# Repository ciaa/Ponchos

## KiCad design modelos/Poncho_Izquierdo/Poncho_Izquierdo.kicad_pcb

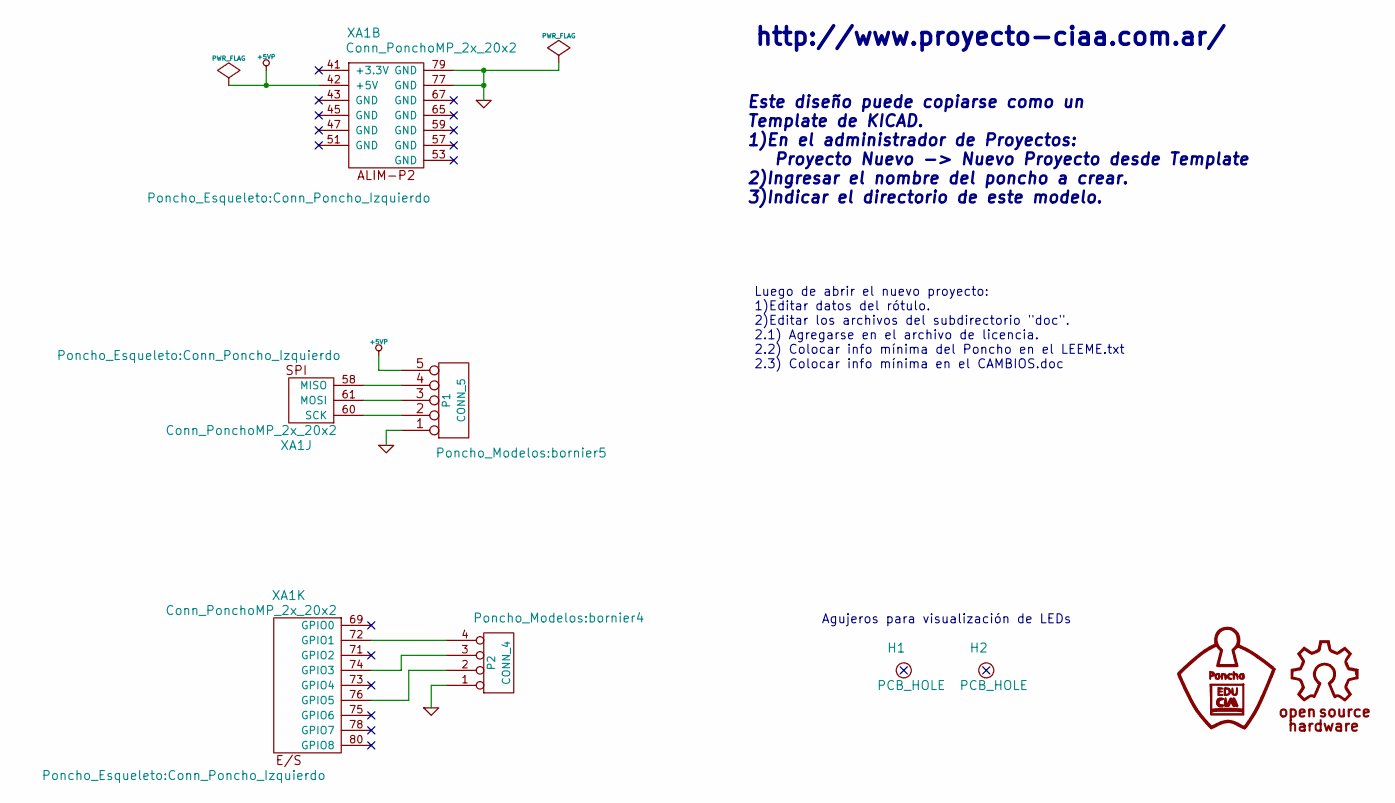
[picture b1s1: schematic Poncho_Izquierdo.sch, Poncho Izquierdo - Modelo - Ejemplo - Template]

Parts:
H1, H2: PCB_HOLE; Led_Hole
P1: CONN_5; bornier5
P2: CONN_4; bornier4
XA1: Conn_PonchoMP_2x_20x2; Conn_Poncho_Izquierdo

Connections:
+5VP: P1.5, XA1.42 (+5V)
GND: P1.1, P2.1, XA1.77 (GND), XA1.79 (GND)
unnamed: P1.2, XA1.60 (SCK)
unnamed: P1.3, XA1.61 (MOSI)
unnamed: P1.4, XA1.58 (MISO)
unnamed: P2.2, XA1.76 (GPIO5)
unnamed: P2.3, XA1.74 (GPIO3)
unnamed: P2.4, XA1.72 (GPIO1)

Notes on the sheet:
Este diseño puede copiarse como un Template de KICAD. 1)En el administrador de Proyectos: Proyecto Nuevo -> Nuevo Proyecto desde Template 2)Ingresar el nombre del poncho a crear. 3)Indicar el directorio de este modelo.
http://www.proyecto-ciaa.com.ar/
Luego de abrir el nuevo proyecto: 1)Editar datos del rótulo. 2)Editar los archivos del subdirectorio "doc". 2.1) Agregarse en el archivo de licencia. 2.2) Colocar info mínima del Poncho en el LEEME.txt 2.3) Colocar info mínima en el CAMBIOS.doc
Agujeros para visualización de LEDs

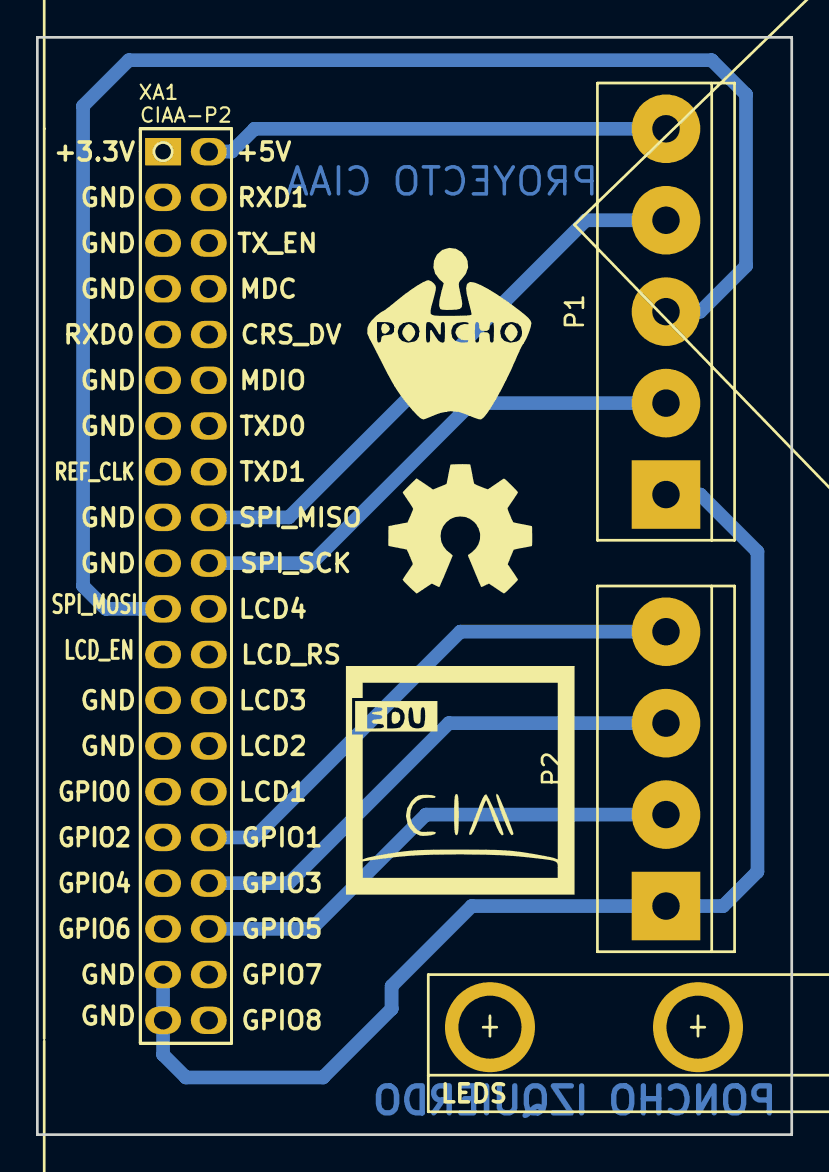
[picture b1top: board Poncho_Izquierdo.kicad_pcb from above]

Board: 2 copper layers, 41.9 x 61.0 mm, 7 parts (0 on the bottom side), 8 nets.

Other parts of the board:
G101: Logo_OSHWA
MP1: Plantilla_EDU-CIAA

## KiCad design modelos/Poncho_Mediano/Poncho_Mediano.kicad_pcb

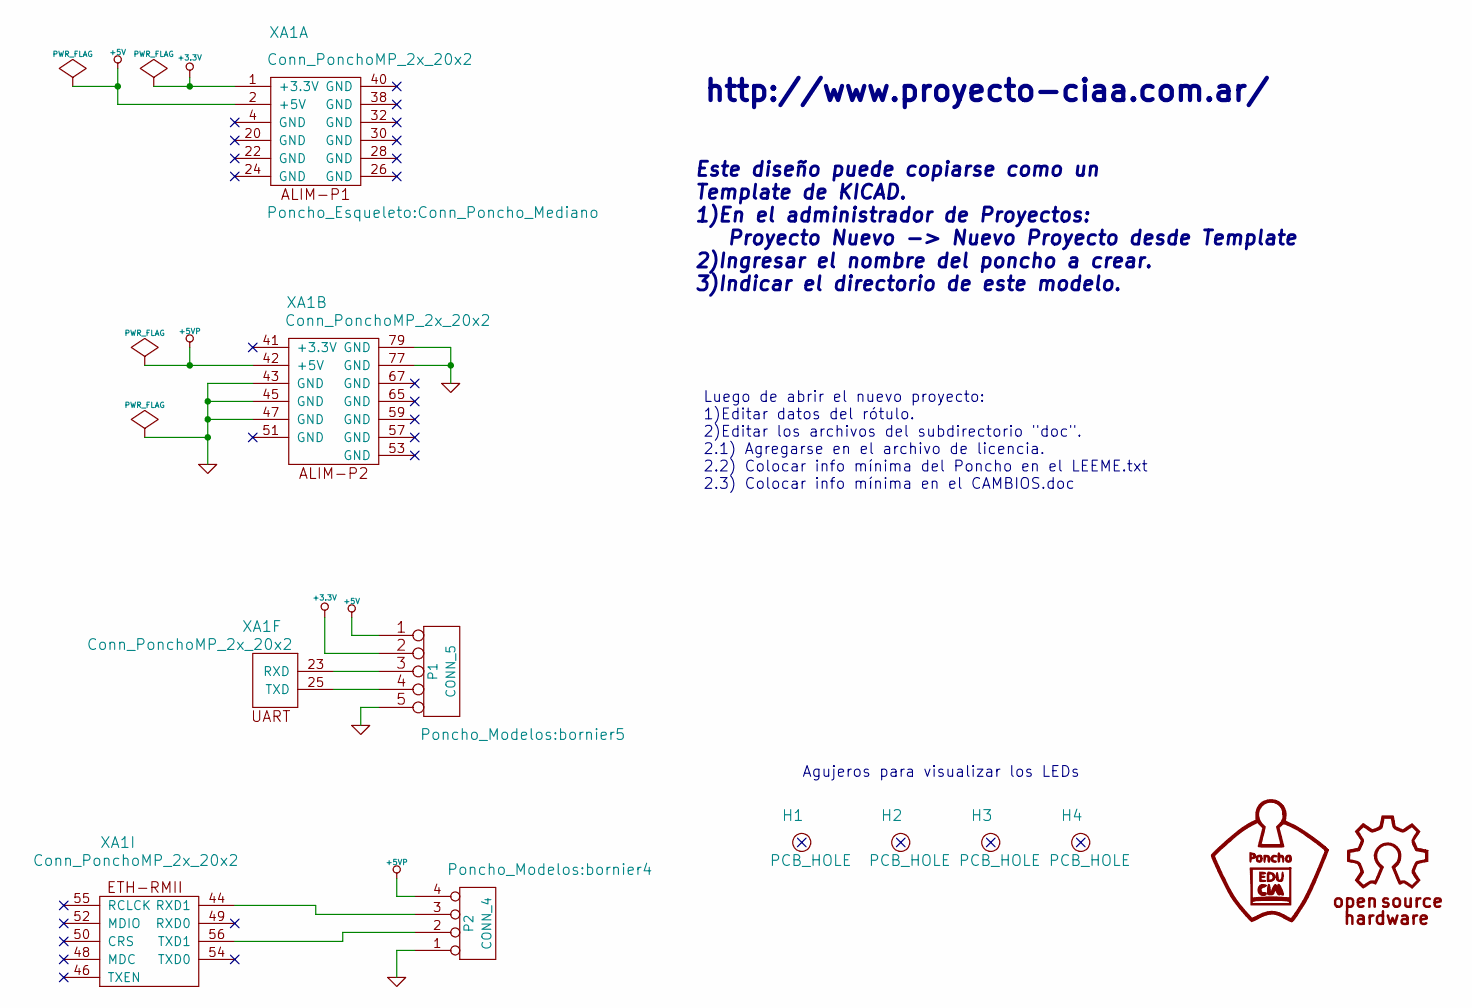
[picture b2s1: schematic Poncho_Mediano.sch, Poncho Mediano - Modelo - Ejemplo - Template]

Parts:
H1, H2, H3, H4: PCB_HOLE; Led_Hole
P1: CONN_5; bornier5
P2: CONN_4; bornier4
XA1: Conn_PonchoMP_2x_20x2; Conn_Poncho_Mediano

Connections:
+3.3V: P1.2, XA1.1 (+3.3V)
+5V: P1.1, XA1.2 (+5V)
+5VP: P2.4, XA1.42 (+5V)
GND: P1.5, P2.1, XA1.43 (GND), XA1.45 (GND), XA1.47 (GND), XA1.77 (GND), XA1.79 (GND)
unnamed: P1.3, XA1.23 (RXD)
unnamed: P1.4, XA1.25 (TXD)
unnamed: P2.2, XA1.56 (TXD1)
unnamed: P2.3, XA1.44 (RXD1)

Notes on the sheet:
Este diseño puede copiarse como un Template de KICAD. 1)En el administrador de Proyectos: Proyecto Nuevo -> Nuevo Proyecto desde Template 2)Ingresar el nombre del poncho a crear. 3)Indicar el directorio de este modelo.
http://www.proyecto-ciaa.com.ar/
Luego de abrir el nuevo proyecto: 1)Editar datos del rótulo. 2)Editar los archivos del subdirectorio "doc". 2.1) Agregarse en el archivo de licencia. 2.2) Colocar info mínima del Poncho en el LEEME.txt 2.3) Colocar info mínima en el CAMBIOS.doc
Agujeros para visualizar los LEDs

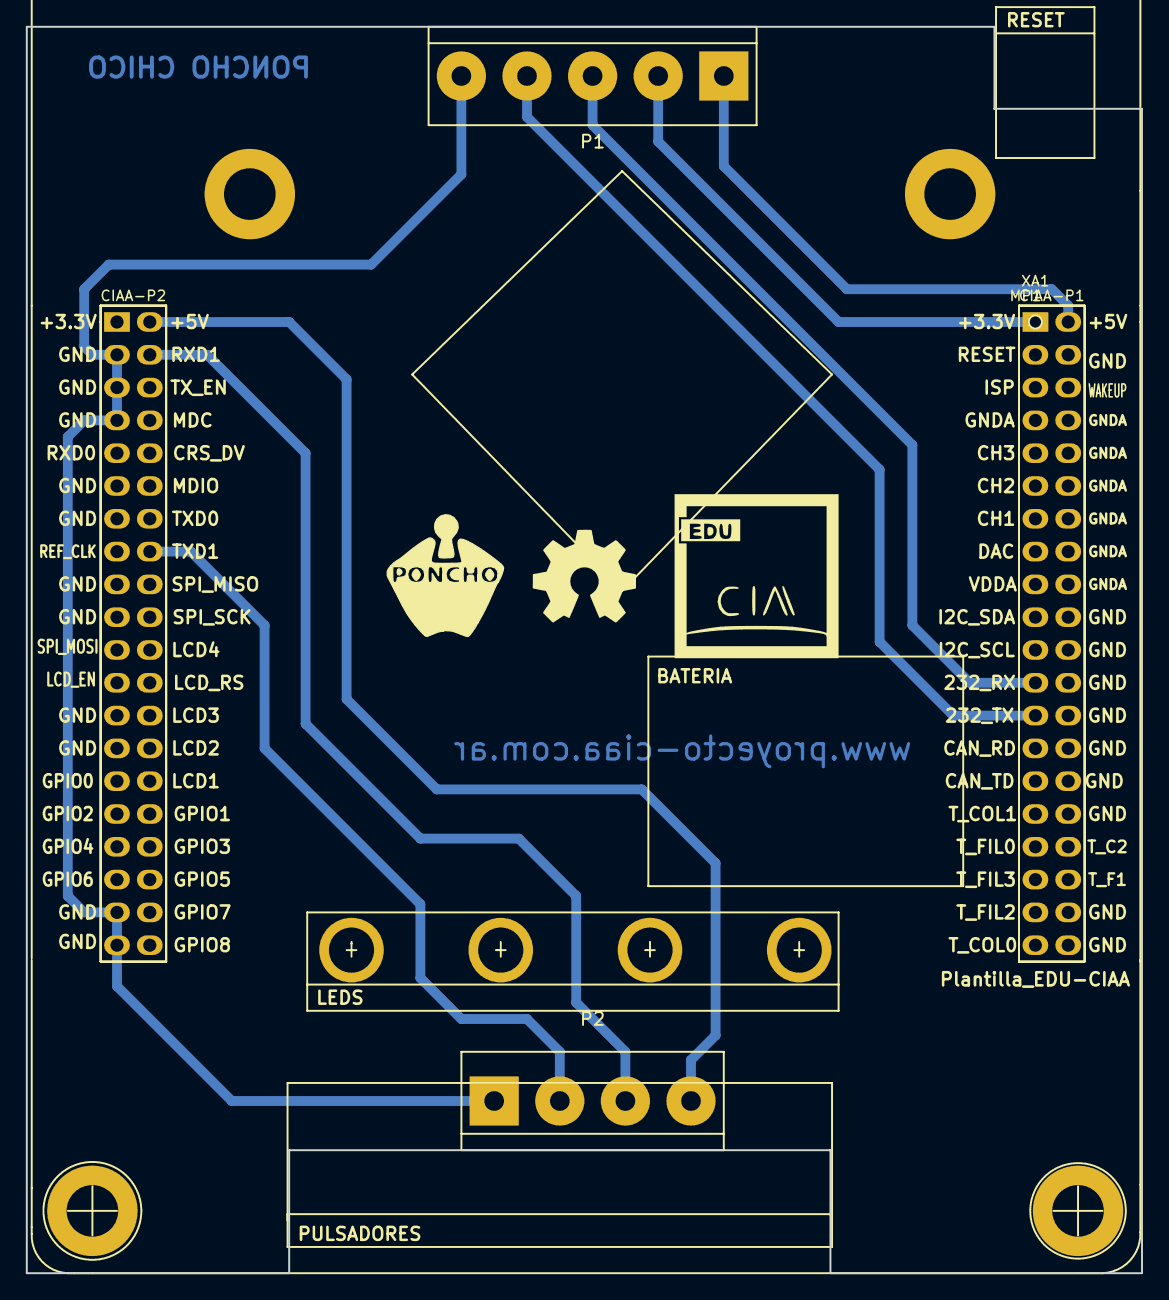
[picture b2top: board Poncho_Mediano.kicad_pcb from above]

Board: 2 copper layers, 86.4 x 96.5 mm, 9 parts (0 on the bottom side), 8 nets.

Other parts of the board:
G101: Logo_OSHWA
MP1: Plantilla_EDU-CIAA

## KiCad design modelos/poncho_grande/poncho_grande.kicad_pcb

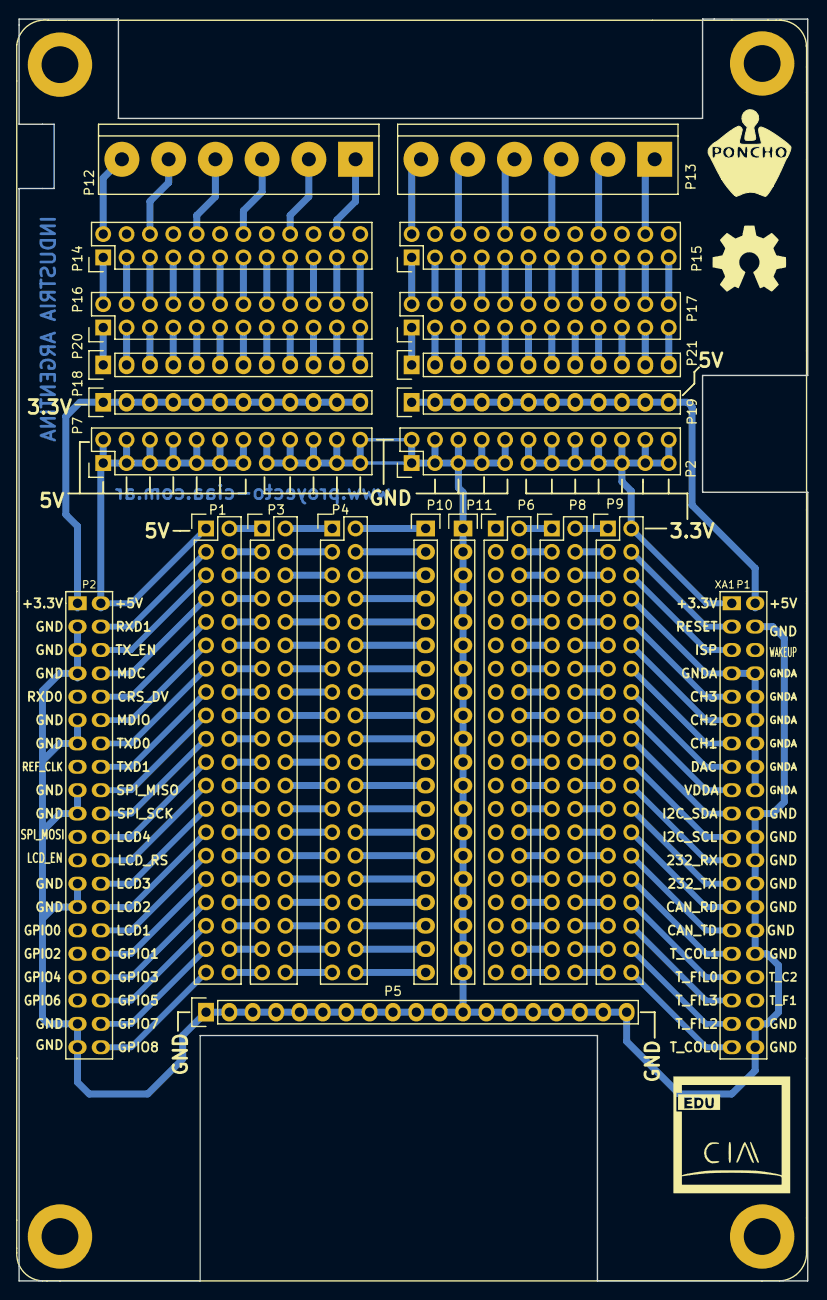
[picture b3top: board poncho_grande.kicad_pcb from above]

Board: 2 copper layers, 85.7 x 137.2 mm, 23 parts (0 on the bottom side), 203 nets.

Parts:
G101: Logo_OSHWA
P1, P3, P4, P6, P8, P9: CONN_02X20; Pin_Header_Straight_2x20
P2, P7: CONN_01X20; Pin_Header_Straight_2x12
P5: CONN_01X19; Pin_Header_Straight_1x19
P10, P11: CONN_01X20; Pin_Header_Straight_1x20
P12, P13: CONN_01X06; bornier6
P14, P15, P16, P17: CONN_02X12; Pin_Header_Straight_2x12
P18, P19, P20, P21: CONN_01X12; Pin_Header_Straight_1x12
XA1: poncho_grande

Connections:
+3.3V: P2.11, P2.12, P2.13, P2.14, P2.15, P2.16, P2.17, P2.18, P2.19, P2.20, P2.21, P2.22, P2.23, P2.24, P9.2, XA1.1
+3.3VADC: P9.18, XA1.17
+3.3VP: P18.1, P18.2, P18.3, P18.4, P18.5, P18.6, P18.7, P18.8, P18.9, P18.10, P18.11, P18.12, XA1.41
+5V: P19.1, P19.2, P19.3, P19.4, P19.5, P19.6, P19.7, P19.8, P19.9, P19.10, P19.11, P19.12, XA1.2
+5VP: P1.1, P7.1, P7.2, P7.3, P7.4, P7.5, P7.6, P7.7, P7.8, P7.9, P7.10, P7.11, P7.12, P7.13, P7.14, XA1.42
/Circuito Principal/ADC1: P9.14, XA1.13
/Circuito Principal/ADC2: P9.12, XA1.11
/Circuito Principal/ADC3: P9.10, XA1.9
/Circuito Principal/COL0: P9.40, XA1.39
/Circuito Principal/COL1: P9.32, XA1.31
/Circuito Principal/CRS: P1.9, XA1.50
/Circuito Principal/DAC: P9.16, XA1.15
/Circuito Principal/F0: P9.34, XA1.33
/Circuito Principal/F2: P9.38, XA1.37
/Circuito Principal/F3: P9.36, XA1.35
/Circuito Principal/GPIO1: P1.31, XA1.72
/Circuito Principal/GPIO3: P1.33, XA1.74
/Circuito Principal/GPIO5: P1.35, XA1.76
/Circuito Principal/GPIO7: P1.37, XA1.78
/Circuito Principal/GPIO8: P1.39, XA1.80
/Circuito Principal/ISP: P9.6, XA1.5
/Circuito Principal/LCD1: P1.29, XA1.70
/Circuito Principal/LCD2: P1.27, XA1.68
/Circuito Principal/LCD3: P1.25, XA1.66
/Circuito Principal/LCD4: P1.21, XA1.62
/Circuito Principal/MDC: P1.7, XA1.48
/Circuito Principal/MDIO: P1.11, XA1.52
/Circuito Principal/MISO: P1.17, XA1.58
/Circuito Principal/RD: P9.28, XA1.27
/Circuito Principal/RESET: P9.4, XA1.3
/Circuito Principal/RS: P1.23, XA1.64
/Circuito Principal/RXD: P9.24, XA1.23
/Circuito Principal/RXD1: P1.3, XA1.44
/Circuito Principal/SCL: P9.22, XA1.21
/Circuito Principal/SDA: P9.20, XA1.19
/Circuito Principal/TD: P9.30, XA1.29
/Circuito Principal/TXD: P9.26, XA1.25
/Circuito Principal/TXD0: P1.13, XA1.54
/Circuito Principal/TXD1: P1.15, XA1.56
/Circuito Principal/TXEN: P1.5, XA1.46
/Circuito Principal/spiCCK: P1.19, XA1.60
GND: P2.1, P2.2, P2.3, P2.4, P2.5, P2.6, P2.7, P2.8, P2.9, P2.10, P5.1, P5.2, P5.3, P5.4, P5.5, P5.6, P5.7, P5.8, P5.9, P5.10, P5.11, P5.12, P5.13, P5.14, P5.15, P5.16, P5.17, P5.18, P5.19, P7.15, P7.16, P7.17, P7.18, P7.19, P7.20, P7.21, P7.22, P7.23, P7.24, P11.1, P11.2, P11.3, P11.4, P11.5, P11.6, P11.7, P11.8, P11.9, P11.10, P11.11, P11.12, P11.13, P11.14, P11.15, P11.16, P11.17, P11.18, P11.19, P11.20, XA1.4, XA1.20, XA1.22, XA1.24, XA1.26, XA1.28, XA1.30, XA1.32, XA1.38, XA1.40, XA1.43, XA1.45, XA1.47, XA1.51, XA1.53, XA1.57, XA1.59, XA1.65, XA1.67, XA1.77, XA1.79
GNDA: P9.8, XA1.7, XA1.8, XA1.10, XA1.12, XA1.14, XA1.16, XA1.18
unnamed: P1.2, P3.1
unnamed: P1.4, P3.3
unnamed: P1.6, P3.5
unnamed: P1.8, P3.7
unnamed: P1.10, P3.9
unnamed: P1.12, P3.11
unnamed: P1.14, P3.13
unnamed: P1.16, P3.15
unnamed: P1.18, P3.17
unnamed: P1.20, P3.19
unnamed: P1.22, P3.21
unnamed: P1.24, P3.23
unnamed: P1.26, P3.25
unnamed: P1.28, P3.27
unnamed: P1.30, P3.29
unnamed: P1.32, P3.31
unnamed: P1.34, P3.33
unnamed: P1.36, P3.35
unnamed: P1.38, P3.37
unnamed: P1.40, P3.39
unnamed: P3.2, P4.1
unnamed: P3.4, P4.3
unnamed: P3.6, P4.5
unnamed: P3.8, P4.7
unnamed: P3.10, P4.9
unnamed: P3.12, P4.11
unnamed: P3.14, P4.13
unnamed: P3.16, P4.15
unnamed: P3.18, P4.17
unnamed: P3.20, P4.19
unnamed: P3.22, P4.21
unnamed: P3.24, P4.23
unnamed: P3.26, P4.25
unnamed: P3.28, P4.27
unnamed: P3.30, P4.29
unnamed: P3.32, P4.31
unnamed: P3.34, P4.33
unnamed: P3.36, P4.35
unnamed: P3.38, P4.37
unnamed: P3.40, P4.39
unnamed: P6.2, P8.1
unnamed: P6.4, P8.3
unnamed: P6.6, P8.5
unnamed: P6.8, P8.7
unnamed: P6.10, P8.9
unnamed: P6.12, P8.11
unnamed: P6.14, P8.13
unnamed: P6.16, P8.15
unnamed: P6.18, P8.17
unnamed: P6.20, P8.19
unnamed: P6.22, P8.21
unnamed: P6.24, P8.23
unnamed: P6.26, P8.25
unnamed: P6.28, P8.27
unnamed: P6.30, P8.29
unnamed: P6.32, P8.31
unnamed: P6.34, P8.33
unnamed: P6.36, P8.35
unnamed: P6.38, P8.37
unnamed: P6.40, P8.39
unnamed: P8.2, P9.1
unnamed: P8.4, P9.3
unnamed: P8.6, P9.5
unnamed: P8.8, P9.7
unnamed: P8.10, P9.9
unnamed: P8.12, P9.11
unnamed: P8.14, P9.13
unnamed: P8.16, P9.15
unnamed: P8.18, P9.17
unnamed: P8.20, P9.19
unnamed: P8.22, P9.21
unnamed: P8.24, P9.23
unnamed: P8.26, P9.25
unnamed: P8.28, P9.27
unnamed: P8.30, P9.29
unnamed: P8.32, P9.31
unnamed: P8.34, P9.33
unnamed: P8.36, P9.35
unnamed: P8.38, P9.37
unnamed: P8.40, P9.39
unnamed: P4.2, P10.1
unnamed: P4.4, P10.2
unnamed: P4.6, P10.3
unnamed: P4.8, P10.4
unnamed: P4.10, P10.5
unnamed: P4.12, P10.6
unnamed: P4.14, P10.7
unnamed: P4.16, P10.8
unnamed: P4.18, P10.9
unnamed: P4.20, P10.10
unnamed: P4.22, P10.11
unnamed: P4.24, P10.12
unnamed: P4.26, P10.13
unnamed: P4.28, P10.14
unnamed: P4.30, P10.15
unnamed: P4.32, P10.16
unnamed: P4.34, P10.17
unnamed: P4.36, P10.18
unnamed: P4.38, P10.19
unnamed: P4.40, P10.20
unnamed: P12.1, P14.22
unnamed: P12.2, P14.18
unnamed: P12.3, P14.14
unnamed: P12.4, P14.10
unnamed: P12.5, P14.6
unnamed: P12.6, P14.2
unnamed: P13.1, P15.22
unnamed: P13.2, P15.18
unnamed: P13.3, P15.14
unnamed: P13.4, P15.10
unnamed: P13.5, P15.6
unnamed: P13.6, P15.2
unnamed: P14.1, P16.2
unnamed: P14.3, P16.4
unnamed: P14.5, P16.6
unnamed: P14.7, P16.8
unnamed: P14.9, P16.10
unnamed: P14.11, P16.12
unnamed: P14.13, P16.14
unnamed: P14.15, P16.16
unnamed: P14.17, P16.18
unnamed: P14.19, P16.20
unnamed: P14.21, P16.22
unnamed: P14.23, P16.24
unnamed: P15.1, P17.2
unnamed: P15.3, P17.4
unnamed: P15.5, P17.6
unnamed: P15.7, P17.8
unnamed: P15.9, P17.10
unnamed: P15.11, P17.12
unnamed: P15.13, P17.14
unnamed: P15.15, P17.16
unnamed: P15.17, P17.18
unnamed: P15.19, P17.20
unnamed: P15.21, P17.22
unnamed: P15.23, P17.24
unnamed: P16.1, P20.1
unnamed: P16.3, P20.2
unnamed: P16.5, P20.3
unnamed: P16.7, P20.4
unnamed: P16.9, P20.5
unnamed: P16.11, P20.6
unnamed: P16.13, P20.7
unnamed: P16.15, P20.8
unnamed: P16.17, P20.9
unnamed: P16.19, P20.10
unnamed: P16.21, P20.11
unnamed: P16.23, P20.12
unnamed: P17.1, P21.1
unnamed: P17.3, P21.2
unnamed: P17.5, P21.3
unnamed: P17.7, P21.4
unnamed: P17.9, P21.5
unnamed: P17.11, P21.6
unnamed: P17.13, P21.7
unnamed: P17.15, P21.8
unnamed: P17.17, P21.9
unnamed: P17.19, P21.10
unnamed: P17.21, P21.11
unnamed: P17.23, P21.12

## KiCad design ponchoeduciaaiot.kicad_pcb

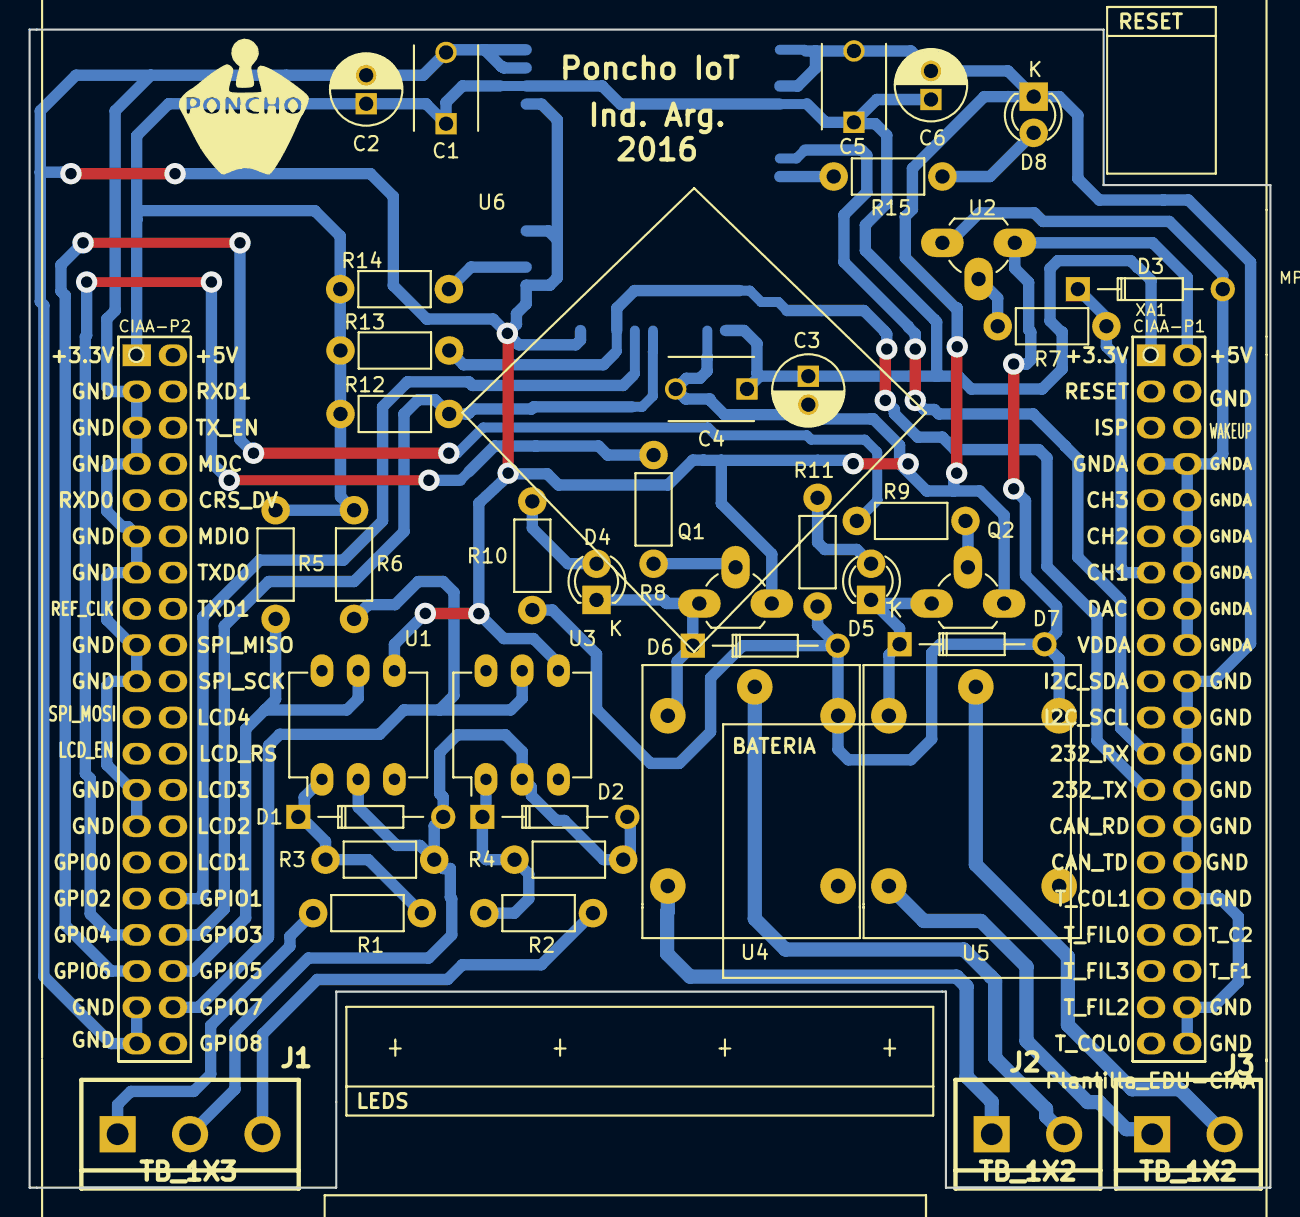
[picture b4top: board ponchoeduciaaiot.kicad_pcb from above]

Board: 2 copper layers, 87.0 x 81.2 mm, 42 parts (0 on the bottom side), 32 nets.

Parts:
C1, C4, C5: 100nF; C_Disc_D6_P5
C2, C3, C6: 2.2uF; C_Radial_D5_L11_P2
D1, D2, D6, D7: 1N4007; Diode_DO-35_SOD27_Horizontal_RM10
D3: 1N4728A; Diode_DO-35_SOD27_Horizontal_RM10
D4, D5, D8: LED; LED-3MM
J1: TB_1X3; bornier3
J2, J3: TB_1X2; bornier2
MP?: Plantilla_EDU-CIAA
Q1, Q2: BC548; TO-92_Rugged
R1, R2: 3.3k; Resistor_Horizontal_RM7mm
R3, R4: 4.7k; Resistor_Horizontal_RM7mm
R5, R6, R8, R9, R12, R14: 10k; Resistor_Horizontal_RM7mm
R7, R15: 150; Resistor_Horizontal_RM7mm
R10, R11: 330; Resistor_Horizontal_RM7mm
R13: 100k; Resistor_Horizontal_RM7mm
U1, U3: 4N25; DIP-6_W7.62mm_LongPads
U2: LM35; TO-92_Rugged
U4, U5: RELAY; Relay5vSI
U6: RN1810E; RN1810
XA1: Conn_Poncho2P_2x_20x2; Conn_Poncho_Mediano

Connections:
+3V3: C1.1, C2.1, C3.1, C4.1, C5.1, C6.1, R5.1, R6.1, R12.1, R13.1, R14.1, U6.4, U6.15, U6.35, XA1.1, XA1.41
+5V: D6.2, D7.2, R10.1, R11.1, U2.1, U4.2, U5.2, XA1.2
/ConectoresPoncho/ANALOG_IN: D3.1, R7.1, XA1.13
/ConectoresPoncho/MODULE_RESET: R12.2, U6.19, XA1.74
/ConectoresPoncho/RXD_EDUCIAA: U6.7, XA1.23
/ConectoresPoncho/TXD_EDUCIAA: R13.2, U6.21, XA1.25
/comm/CMD_CTRL: U6.20, XA1.72
/gpios/IN0: R5.2, U1.5, XA1.76
/gpios/IN1: R6.2, U3.5, XA1.78
/gpios/OUT0: R8.2, XA1.73
/gpios/OUT1: R9.2, XA1.75
GND: C1.2, C2.2, C3.2, C4.2, C5.2, C6.2, D8.1, Q1.3, Q2.3, U1.4, U3.4, U6.1, U6.3, U6.16, U6.23, U6.24, U6.27, U6.34, U6.36, U6.37, XA1.20, XA1.22, XA1.24, XA1.26, XA1.28, XA1.30, XA1.32, XA1.38, XA1.40, XA1.43, XA1.45, XA1.47, XA1.51, XA1.53, XA1.57, XA1.59, XA1.65, XA1.67, XA1.77, XA1.79
GNDA: D3.2, U2.3, XA1.7, XA1.8, XA1.10, XA1.12, XA1.14, XA1.16, XA1.18
unnamed: D1.1, R1.1, R3.1, U1.1
unnamed: D1.2, D2.2, J1.2, R3.2, R4.2, U1.2, U3.2
unnamed: D2.1, R2.1, R4.1, U3.1
unnamed: D4.1, D6.1, Q1.1, U4.1
unnamed: D4.2, R10.2
unnamed: D5.1, D7.1, Q2.1, U5.1
unnamed: D5.2, R11.2
unnamed: D8.2, R15.1
unnamed: J1.1, R1.2
unnamed: J1.3, R2.2
unnamed: J2.1, U4.4
unnamed: J2.2, U4.3
unnamed: J3.1, U5.4
unnamed: J3.2, U5.3
unnamed: Q1.2, R8.1
unnamed: Q2.2, R9.1
unnamed: R7.2, U2.2
unnamed: R14.2, U6.25
unnamed: R15.2, U6.8

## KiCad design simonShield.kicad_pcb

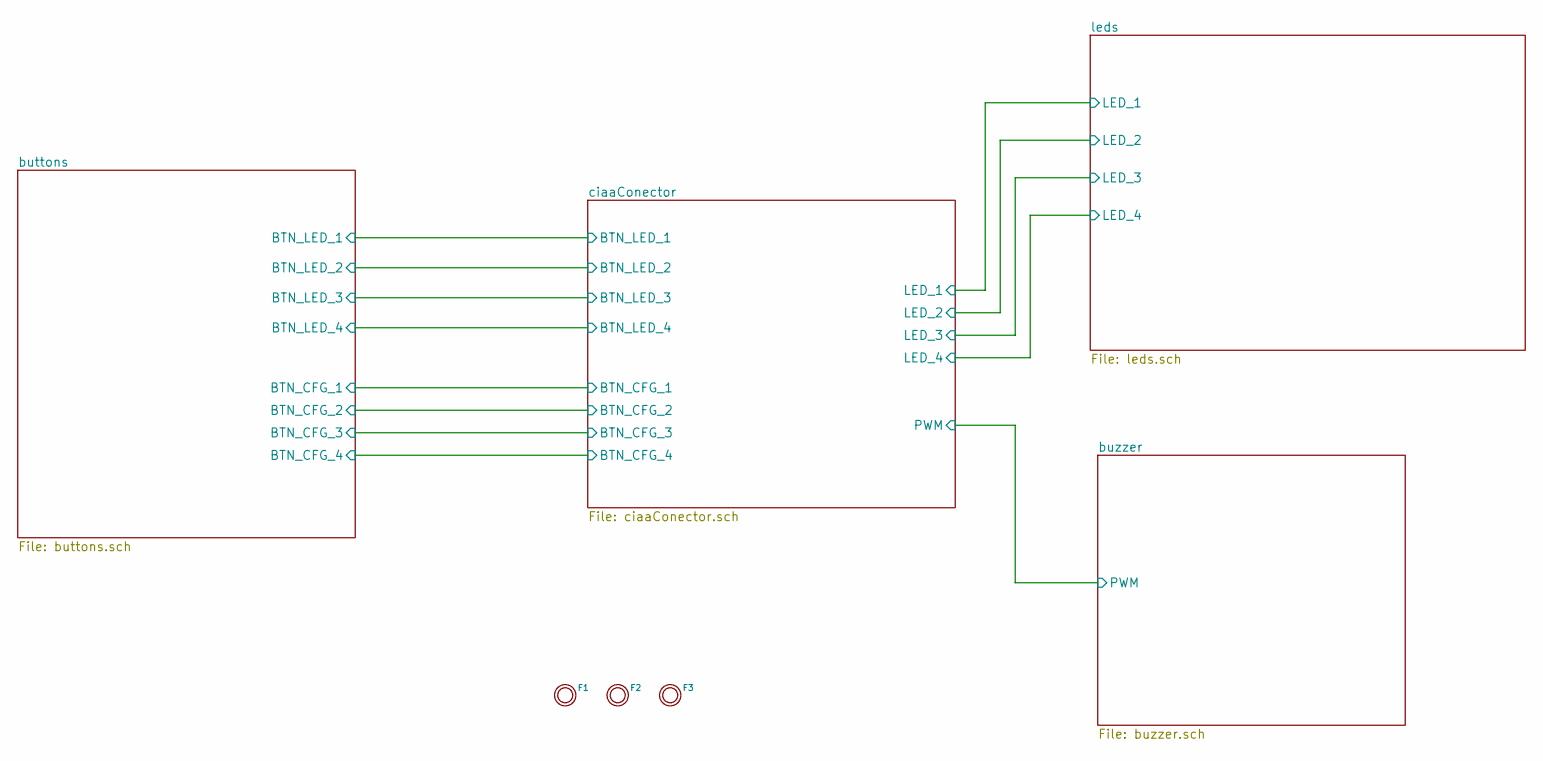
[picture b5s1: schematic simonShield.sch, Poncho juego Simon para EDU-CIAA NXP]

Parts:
F1, F2, F3: FIDUCIAL; Fiducial_1mm

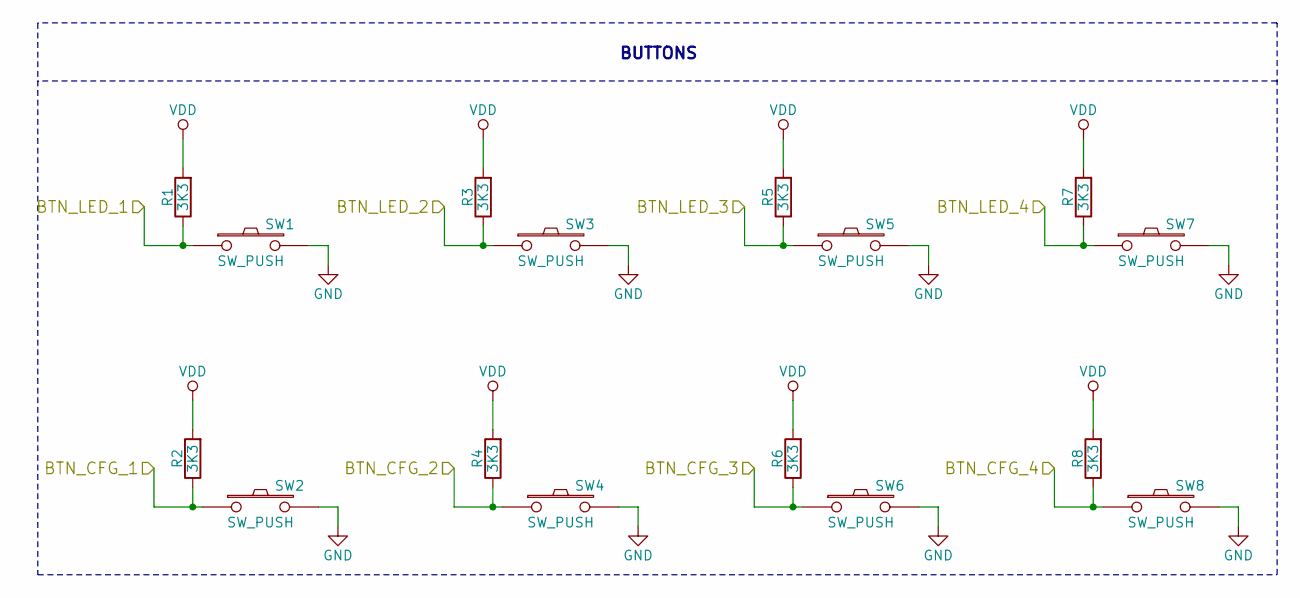
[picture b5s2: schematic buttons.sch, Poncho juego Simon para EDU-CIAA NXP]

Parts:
R1, R2, R3, R4, R5, R6, R7, R8: 3K3; Resistor_Horizontal_RM7mm; Digikey# 680EBK­ND
SW1, SW2, SW3, SW4, SW5, SW6, SW7, SW8: SW_PUSH; SW_PUSH_SMALL; Digikey# 450­1804­ND

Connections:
/buttons/BTN_CFG_1: R2.1, SW2.1; also elsewhere on the board
/buttons/BTN_CFG_2: R4.1, SW4.1; also elsewhere on the board
/buttons/BTN_CFG_3: R6.1, SW6.1; also elsewhere on the board
/buttons/BTN_CFG_4: R8.1, SW8.1; also elsewhere on the board
/buttons/BTN_LED_1: R1.1, SW1.1; also elsewhere on the board
/buttons/BTN_LED_2: R3.1, SW3.1; also elsewhere on the board
/buttons/BTN_LED_3: R5.1, SW5.1; also elsewhere on the board
/buttons/BTN_LED_4: R7.1, SW7.1; also elsewhere on the board
GND: SW1.2, SW2.2, SW3.2, SW4.2, SW5.2, SW6.2, SW7.2, SW8.2; also elsewhere on the board
VCC: R1.2, R2.2, R3.2, R4.2, R5.2, R6.2, R7.2, R8.2; also elsewhere on the board

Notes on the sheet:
BUTTONS

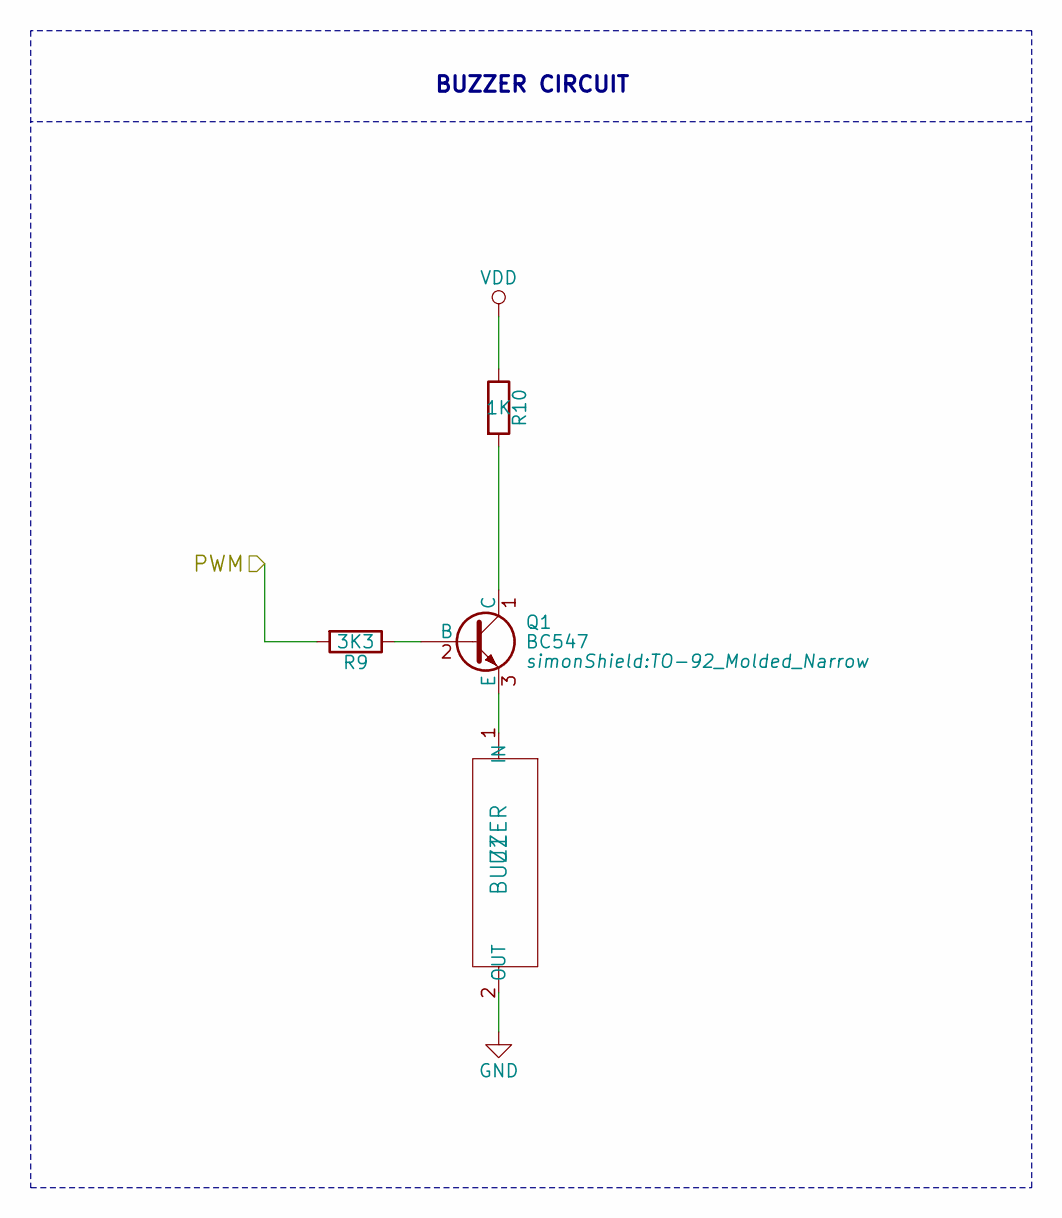
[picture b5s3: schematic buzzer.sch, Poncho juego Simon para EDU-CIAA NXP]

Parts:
Q1: BC547; TO-92_Molded_Narrow; Digikey# BC33725TACT-ND
R9: 3K3; Resistor_Horizontal_RM7mm; Digikey# 680EBK-ND
R10: 1K; Resistor_Horizontal_RM7mm; Digikey# 680EBK-ND
U1: BUZZER; MagneticBuzzer_ProSignal_ABT-410-RC; Digikey# 445-2525-1-ND

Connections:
/ciaaConector/PWM: R9.2; also elsewhere on the board
GND: U1.2 (OUT); also elsewhere on the board
unnamed: Q1.1 (C), R10.2
unnamed: Q1.2 (B), R9.1
unnamed: Q1.3 (E), U1.1 (IN)
VCC: R10.1; also elsewhere on the board

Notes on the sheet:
BUZZER CIRCUIT

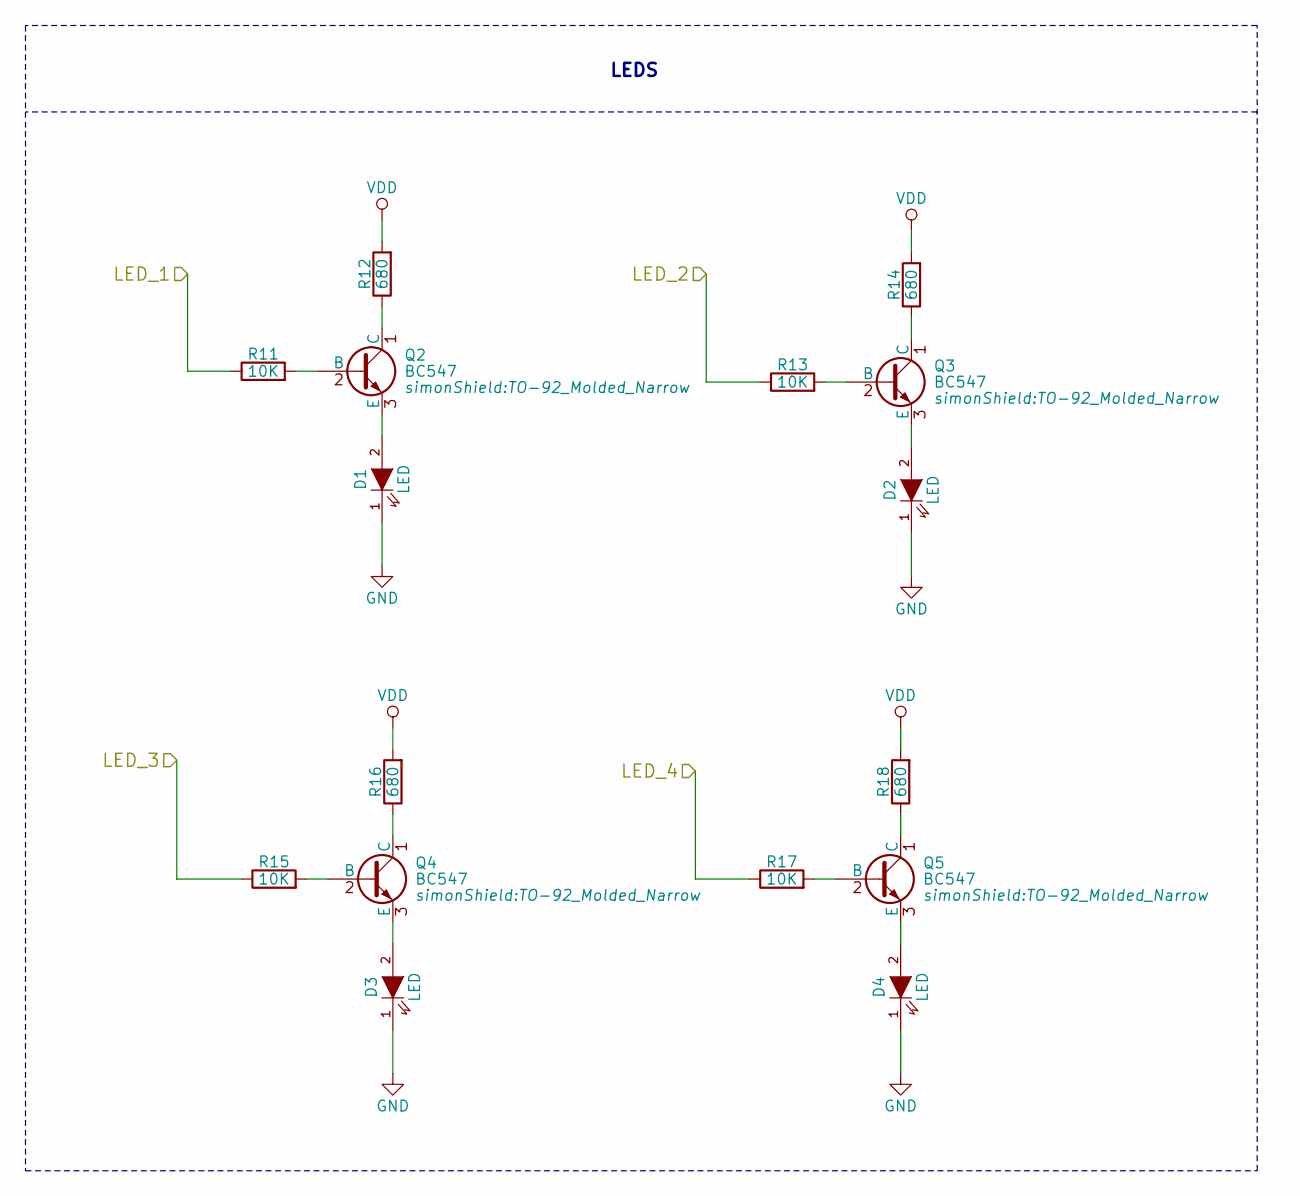
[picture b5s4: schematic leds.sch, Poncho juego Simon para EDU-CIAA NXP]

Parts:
D1, D2, D3, D4: LED; LED-5MM; Digikey# 1497-1031-ND
Q2, Q3, Q4, Q5: BC547; TO-92_Molded_Narrow; Digikey# BC33725TACT-ND
R11, R13, R15, R17: 10K; Resistor_Horizontal_RM7mm; Digikey# 680EBK-ND
R12, R14, R16, R18: 680; Resistor_Horizontal_RM7mm; Digikey# 680EBK-ND

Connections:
/ciaaConector/LED_1: R11.1; also elsewhere on the board
/ciaaConector/LED_2: R13.1; also elsewhere on the board
/ciaaConector/LED_3: R15.1; also elsewhere on the board
/ciaaConector/LED_4: R17.1; also elsewhere on the board
GND: D1.1 (K), D2.1 (K), D3.1 (K), D4.1 (K); also elsewhere on the board
unnamed: D1.2 (A), Q2.3 (E)
unnamed: D2.2 (A), Q3.3 (E)
unnamed: D3.2 (A), Q4.3 (E)
unnamed: D4.2 (A), Q5.3 (E)
unnamed: Q2.1 (C), R12.1
unnamed: Q2.2 (B), R11.2
unnamed: Q3.1 (C), R14.1
unnamed: Q3.2 (B), R13.2
unnamed: Q4.1 (C), R16.1
unnamed: Q4.2 (B), R15.2
unnamed: Q5.1 (C), R18.1
unnamed: Q5.2 (B), R17.2
VCC: R12.2, R14.2, R16.2, R18.2; also elsewhere on the board

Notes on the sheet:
LEDS

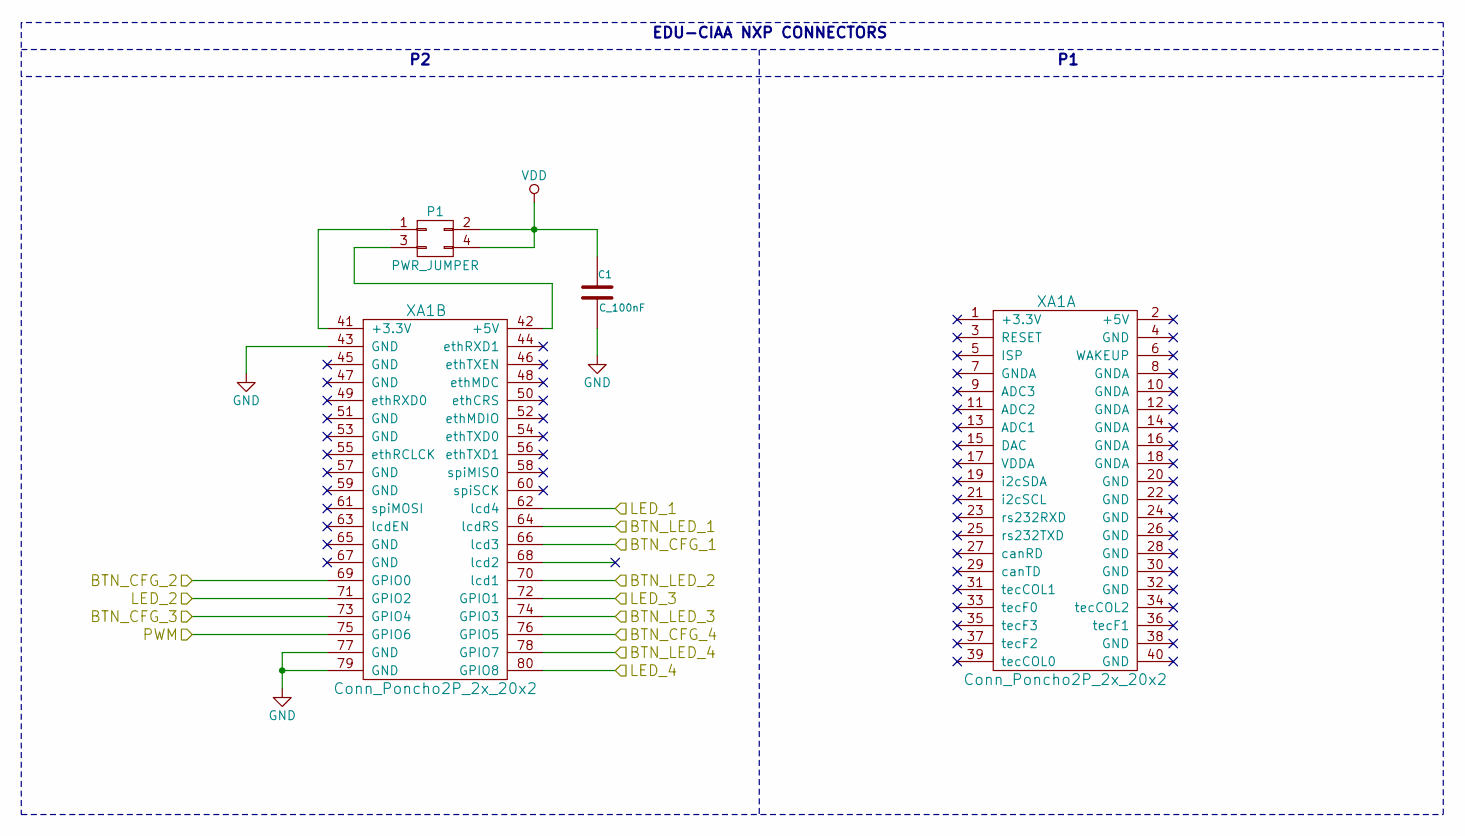
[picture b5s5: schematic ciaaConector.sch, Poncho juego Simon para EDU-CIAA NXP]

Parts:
C1: C_100nF; C_Disc_D3_P2.5; Digikey# BC1160TR­ND
P1: PWR_JUMPER; Pin_Header_Straight_2x02; Digikey# 952­2121­ND
XA1: Conn_Poncho2P_2x_20x2; Conn_Poncho_SinBorde; Digikey# 952­2121­ND

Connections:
/buttons/BTN_CFG_1: XA1.66 (lcd3); also elsewhere on the board
/buttons/BTN_CFG_2: XA1.69 (GPIO0); also elsewhere on the board
/buttons/BTN_CFG_3: XA1.74 (GPIO3); also elsewhere on the board
/buttons/BTN_CFG_4: XA1.76 (GPIO5); also elsewhere on the board
/buttons/BTN_LED_1: XA1.64 (lcdRS); also elsewhere on the board
/buttons/BTN_LED_2: XA1.70 (lcd1); also elsewhere on the board
/buttons/BTN_LED_3: XA1.73 (GPIO4); also elsewhere on the board
/buttons/BTN_LED_4: XA1.78 (GPIO7); also elsewhere on the board
/ciaaConector/LED_1: XA1.62 (lcd4); also elsewhere on the board
/ciaaConector/LED_2: XA1.71 (GPIO2); also elsewhere on the board
/ciaaConector/LED_3: XA1.72 (GPIO1); also elsewhere on the board
/ciaaConector/LED_4: XA1.80 (GPIO8); also elsewhere on the board
/ciaaConector/PWM: XA1.75 (GPIO6); also elsewhere on the board
GND: C1.2, XA1.43 (GND), XA1.77 (GND), XA1.79 (GND); also elsewhere on the board
unnamed: P1.1, XA1.41 (+3.3V)
unnamed: P1.3, XA1.42 (+5V)
VCC: C1.1, P1.2, P1.4; also elsewhere on the board

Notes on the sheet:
EDU-CIAA NXP CONNECTORS

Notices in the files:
ponchoeduciaaiot.kicad_pcb:
License: GPL3
